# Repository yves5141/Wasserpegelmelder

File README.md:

# Wasserpegelmelder

## Übersicht

Der **Wasserpegelmelder** ist ein eigenständiges Überwachungssystem zur Frühwarnung vor Hochwasser. Das Gerät kann an Brücken montiert werden und misst kontinuierlich den Wasserstand des Flusses. Bei Überschreiten kritischer Schwellwerte wird automatisch eine Warnung versendet.

## Funktionsweise

Der Ultraschallsensor JSN-SR04 misst den Abstand vom Sensor zur Wasseroberfläche. Auf Basis dieses Abstands und der Neigung wird der aktuelle Wasserstand berechnet. Das System überwacht dabei:

- **Wasserstand**: kritisch falls >=95 cm (Hälfte der Flussbett-Tiefe von 190 cm)
- **Anstieg**: kritisch falls >=95 cm/h

Bei Erreichen/Überschreiten dieser Werte wird eine Warnmeldung per Telegram versendet.

## Hardware

Das System basiert auf einem **ESP32-WROOM-32U** und verfügt über:

| Komponente | Beschreibung |
|------------|--------------|
| JSN-SR04T | Ultraschallsensor für Wasserstandsmessung |
| LoRa Ra-02 | Funkmodul für zusätzliche Langstreckenkommunikation |
| CN3791 MPPT | Solarladeregler für 9V Solarzelle (1,17W) |
| TPS63901 | Buck-Boost Regler für 3,3V |
| TPS63802 | Buck-Boost Regler für 5V |
| 18650 | Akkuhalterungen für Akkubetrieb |

### JSN-SR04T

## Betriebsmodi

### Modus 1 - Messung
Das Gerät führt alle 20 Sekunden Messungen durch und geht zwischen den Messungen in den Deep-Sleep Modus, um Strom zu sparen. Keine WLAN-Verbindung wird hergestellt.

### Modus 2 - Fernsteuerung
Alle 5 Minuten wird eine WLAN-Verbindung hergestellt, um auf eingehende Telegram-Befehle zu prüfen und ggf. zu antworten. Anschließend geht das Gerät wieder in den Deep-Sleep Modus.

## Telegram-Befehle

Das Gerät verfügt über einen integrierten Telegram-Bot mit folgenden Befehlen:

| Befehl | Parameter | Ausgabe |
|--------|-----------|---------|
| `/meldung` | - | Statusbericht mit aktuellem Wasserstand und Anstiegsgeschwindigkeit |
| `/update` | angehangene FW-Datei | Firmware-Update |

Nur Nachrichten von autorisierten User-IDs werden entgegengenommen und beantwortet.

## Energieeffizienz

Durch Deep-Sleep-Modi und das Abschalten von nicht benötigten Spannungsreglern wird der Stromverbrauch minimiert. Das System ist so ausgelegt, dass es durch die Solarzelle und die 18650 Akkus langfristig eigenständig betrieben werden kann.

## Anwendungsbereich

Das System ist für den Einsatz an einer Brücke gedacht:
- Vorwarnung bei steigendem Wasserstand
- Beobachtung von Anstiegsgeschwindigkeiten
- Langzeitüberwachung des Wasserpegels

Die Installation erfolgt einfach am Geländer mit einer Neigung von ca. 45° zum Lot. Dieser Winkel ergibt sich aus dem Streuwinkel des Sensors zzgl. Toleranz.

## Status und Ausblick

Die Hardwaretests sind abgeschlossen.
Die Softwareimplementierung befindet sich noch in Arbeit.

## Technische Hintergründe

Das Projekt basiert auf einem ESP32-WROOM-32U Modul. Als primäre Kommunikationsschnittstelle dient das integrierte WLAN des ESP32.
Falls lokal kein Hotspot verfügbar ist, kann alternativ auch ein LoRa Funkmodul genutzt werden.
Im Ordner "Hardware" findet sich das KiCAD Projekt für die Hardware.

## 3D Render eines vollbestückten Melders

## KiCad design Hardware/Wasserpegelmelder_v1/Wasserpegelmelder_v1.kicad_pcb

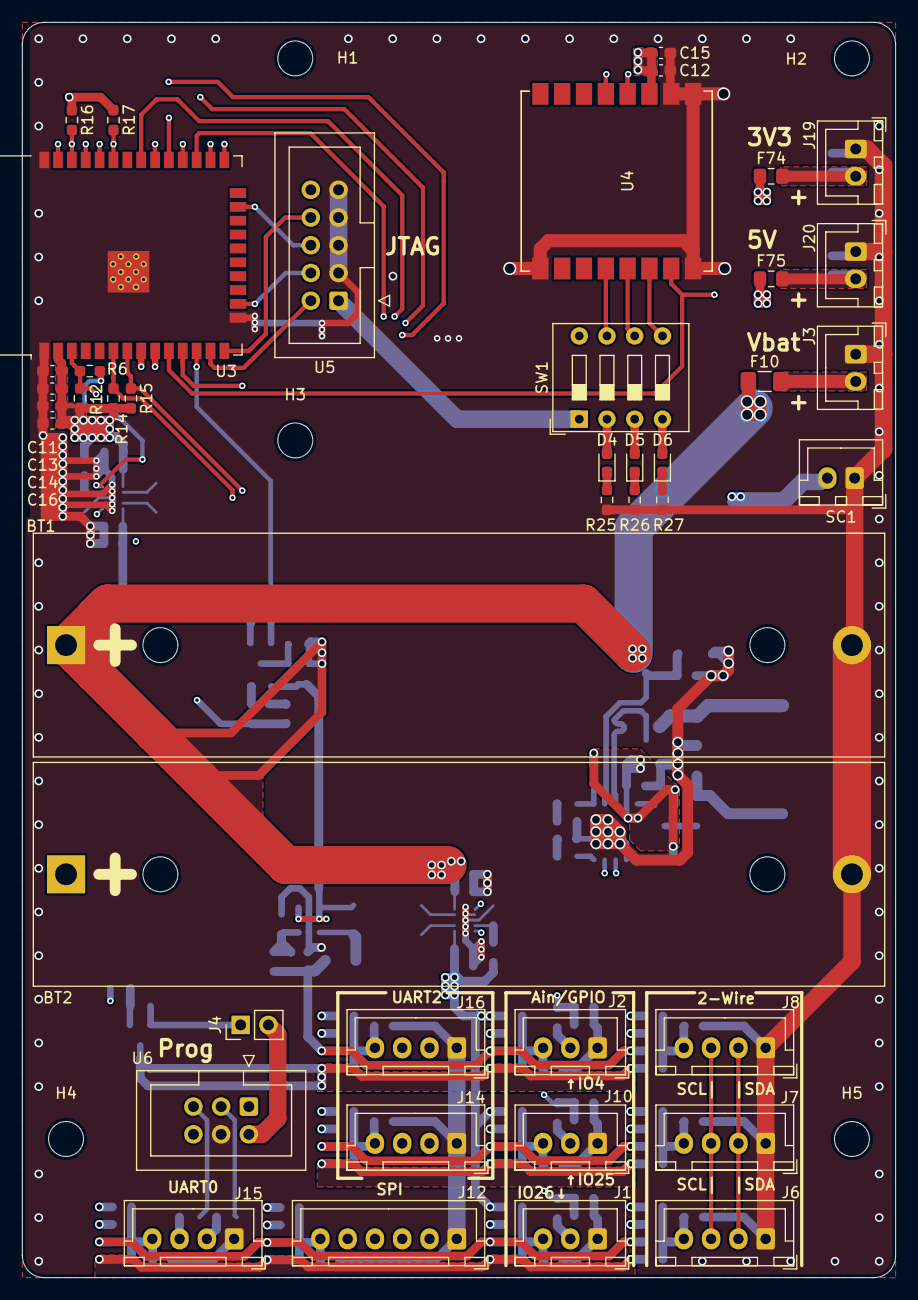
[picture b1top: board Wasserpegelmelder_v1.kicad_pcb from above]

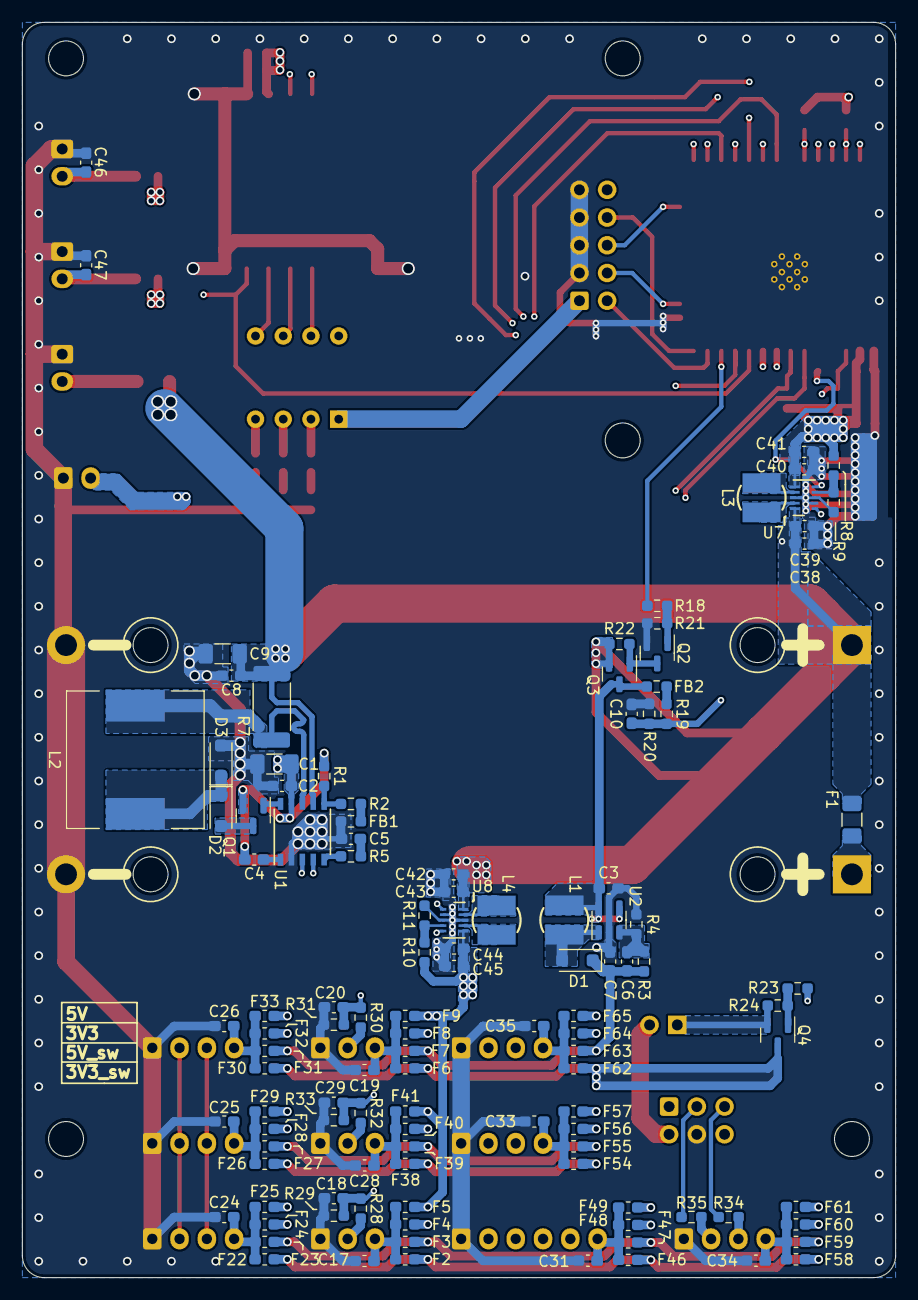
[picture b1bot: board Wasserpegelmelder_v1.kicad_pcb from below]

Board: 4 copper layers, 80.0 x 115.0 mm, 164 parts (116 on the bottom side), 81 nets.

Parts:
BT1, BT2: Battery_Cell; BatteryHolder_1x_18650
C1, C9: 100µF; C_1206_3216Metric_Pad1.33x1.80mm_HandSolder
C2, C4, C8, C11, C12, C39, C40, C43, C44: 100nF; C_0603_1608Metric_Pad1.08x0.95mm_HandSolder
C3: 10µF; C_0603_1608Metric_Pad1.08x0.95mm_HandSolder
C5: 220nF; C_0603_1608Metric_Pad1.08x0.95mm_HandSolder
C6: 71nF; C_0603_1608Metric_Pad1.08x0.95mm_HandSolder
C7, C13: 1µF; C_0603_1608Metric_Pad1.08x0.95mm_HandSolder
C10, C18, C20, C29: 10nF; C_0603_1608Metric_Pad1.08x0.95mm_HandSolder
C14, C15, C16, C17, C19, C24, C25, C26, C28, C31, C33, C34, C35, C38, C41, C42, C45, C46, C47: 47µF; C_0603_1608Metric_Pad1.08x0.95mm_HandSolder
D1, D2, D3: D_Schottky; D_SOD-123F
D4, D5, D6: LED; LED_0603_1608Metric_Pad1.05x0.95mm_HandSolder
F1: 2A; Fuse_1206_3216Metric_Pad1.42x1.75mm_HandSolder
F2, F3, F4, F5, F6, F7, F8, F9, F22, F23, F24, F25, F26, F27, F28, F29, F30, F31, F32, F33, F38, F39, F40, F41, F46, F47, F48, F49, F54, F55, F56, F57, F58, F59, F60, F61, F62, F63, F64, F65: 100mA; Fuse_0603_1608Metric_Pad1.05x0.95mm_HandSolder
F10: 3A; Fuse_1206_3216Metric_Pad1.42x1.75mm_HandSolder
F74, F75: 100mA; Fuse_0805_2012Metric_Pad1.15x1.40mm_HandSolder
FB1, FB2: FerriteBead; R_0603_1608Metric_Pad0.98x0.95mm_HandSolder
H1, H2, H3, H4, H5: MountingHole; MountingHole_3.2mm_M3
J1, J2, J10: IO_ADC; JST_XH_B3B-XH-A_1x03_P2.50mm_Vertical
J3: BatterySupply; JST_XH_B2B-XH-A_1x02_P2.50mm_Vertical
J4: Prog_Jumper; PinHeader_1x02_P2.54mm_Vertical
J6, J7, J8: IO19_IO23; JST_XH_B4B-XH-A_1x04_P2.50mm_Vertical
J12: SPI_Connector; JST_XH_B6B-XH-A_1x06_P2.50mm_Vertical
J14, J16: UART2; JST_XH_B4B-XH-A_1x04_P2.50mm_Vertical
J15: UART0; JST_XH_B4B-XH-A_1x04_P2.50mm_Vertical
J19, J20: nonSwitchedVoltage; JST_XH_B2B-XH-A_1x02_P2.50mm_Vertical
L1: 10µH; CD32_Inductor
L2: 47µH; L_12x12mm_H8mm
L3, L4: 2.2µH; CD32_Inductor
Q1, Q3, Q4: AO3401A; SOT-23
Q2: AO3400A; SOT-23
R1, R2, R3, R4, R8, R9, R10, R11, R19, R20, R25, R26, R27, R28, R29, R30, R31, R32, R33: R; R_0603_1608Metric_Pad0.98x0.95mm_HandSolder
R5: 120R; R_0603_1608Metric_Pad0.98x0.95mm_HandSolder
R6: 0R; R_0603_1608Metric_Pad0.98x0.95mm_HandSolder
R7: R060; R_2512_6332Metric_Pad1.40x3.35mm_HandSolder
R12: 100k; R_0603_1608Metric_Pad0.98x0.95mm_HandSolder
R14, R15: 1M; R_0603_1608Metric_Pad0.98x0.95mm_HandSolder
R16, R17, R34, R35: 1k; R_0603_1608Metric_Pad0.98x0.95mm_HandSolder
R18, R23: 150R; R_0603_1608Metric_Pad0.98x0.95mm_HandSolder
R21, R22, R24: 10k; R_0603_1608Metric_Pad0.98x0.95mm_HandSolder
SC1: 9V_Solar_Cell; JST_XH_B2B-XH-A_1x02_P2.50mm_Vertical
SW1: SW_DIP_x04; SW_DIP_SPSTx04_Slide_9.78x12.34mm_W7.62mm_P2.54mm
U1: SSOP-10_3.9x4.9mm_P1.00mm
U2: TPS61041DBV; SOT-23-5
U3: ESP32-WROOM-32D
U4: Ai-Thinker-Ra-02; Ai-Thinker-Ra-02-LoRa
U5: IDC-Header_2x05_P2.54mm_Vertical
U6: ESP32_Debugger_Prog_IDC-Header_2x03_P2.54mm_Vertical
U7, U8: TPS63802_DFN-10-1EP_2x3mm_P0.5mm_EP0.64x2.4mm

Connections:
3V3_switch: R23.1, U3.8 (IO32)
3V3_switched: F2.1, F6.1, F22.1, F26.1, F30.1, F38.1, F46.1, F54.1, F58.1, F62.1, Q4.3 (D)
5V_switched: C6.1, C7.1, D1.1 (K), F3.1, F7.1, F23.1, F27.1, F31.1, F39.1, F47.1, F55.1, F59.1, F63.1, R3.1
+3V3: C11.1, C12.1, C13.1, C14.1, C15.1, C16.1, C40.1, C41.1, F4.1, F8.1, F24.1, F28.1, F32.1, F40.1, F48.1, F56.1, F60.1, F64.1, F74.1, J4.1, Q4.2 (S), R8.1, R12.2, R14.2, R15.2, R16.1, R17.1, R24.2, SW1.8, U3.2 (VDD), U4.3 (VDD), U7.6 (Vout)
+5V: C44.1, C45.1, F5.1, F9.1, F25.1, F29.1, F33.1, F41.1, F49.1, F57.1, F61.1, F65.1, F75.1, R10.1, U8.6 (Vout)
+BATT: BT1.1 (+), C8.1, C9.1, C38.1, C39.1, C42.1, C43.1, F1.1, F10.1, Q3.2 (S), R7.2, R22.1, U1.7 (BAT), U7.1 (En), U7.10 (Vin), U8.1 (En), U8.10 (Vin)
/Sense_P: L2.2, R7.1, U1.8 (CSP)
/TPS63802_voltage_regulator1/FB: R10.2, R11.1, U8.4 (FB)
/TPS63802_voltage_regulator/FB: R8.2, R9.1, U7.4 (FB)
/TPS63802_voltage_regulator/PG: R6.2, U7.5 (PG)
Ain_Vbat: C10.1, R19.2, R20.1, U3.9 (IO33)
EN: R6.1, R12.1, U3.3 (EN), U6.1 (EN)
GND: BT1.2 (-), BT2.2 (-), C1.2, C2.2, C3.2, C5.2, C7.2, C8.2, C9.2, C10.2, C11.2, C12.2, C13.2, C14.2, C15.2, C16.2, C17.2, C18.2, C19.2, C20.2, C24.2, C25.2, C26.2, C28.2, C29.2, C31.2, C33.2, C34.2, C35.2, C38.2, C39.2, C40.2, C41.2, C42.2, C43.2, C44.2, C45.2, C46.2, C47.2, D3.2 (A), FB1.2, J1.1, J2.1, J3.1, J6.1, J7.1, J8.1, J10.1, J12.1, J14.1, J15.1, J16.1, J19.1, J20.1, Q2.2 (S), R4.2, R9.2, R11.2, R20.2, R21.2, R25.2, R26.2, R27.2, R29.1, R31.1, R33.1, SC1.1 (+), U1.2 (GND), U2.2 (GND), U3.1 (GND), U3.15 (GND), U3.38 (GND), U3.39 (GND), U4.1 (GND), U4.2 (GND), U4.9 (GND), U4.16 (GND), U5.3 (GND), U5.5 (GND), U5.7 (GND), U5.9 (GND), U6.4 (GND), U7.2 (Mode), U7.3 (AGND), U7.8 (GND), U8.2 (Mode), U8.3 (AGND), U8.8 (GND)
IO0: U3.25 (IO0), U6.6 (IO0)
IO4: C20.1, R30.1, R31.2, U3.26 (IO4), U4.5 (DIO0)
IO5: J12.5, U3.29 (IO5)
IO25: C29.1, R32.1, R33.2, U3.10 (IO25), U4.15 (~NSS)
IO26: C18.1, R28.1, R29.2, U3.11 (IO26), U4.4 (~RESET)
MISO: J12.3, SW1.6, U3.31 (IO19), U4.13 (MISO)
MOSI: J12.4, SW1.5, U3.37 (IO23), U4.14 (MOSI)
unnamed: BT2.1 (+), F1.2
unnamed: C5.1, R5.2
unnamed: D1.2 (A), L1.2, U2.1 (SW)
unnamed: D2.2 (A), Q1.3 (D)
unnamed: D2.1 (K), D3.1 (K), L2.1
unnamed: D4.2 (A), SW1.2
unnamed: D4.1 (K), R25.1
unnamed: D5.2 (A), SW1.3
unnamed: D5.1 (K), R26.1
unnamed: D6.2 (A), SW1.4
unnamed: D6.1 (K), R27.1
unnamed: FB1.1, R2.2
unnamed: FB2.1, R19.1
unnamed: J1.2, R28.2
unnamed: C17.1, F2.2, F3.2, F4.2, F5.2, J1.3
unnamed: J2.2, R30.2
unnamed: C19.1, F6.2, F7.2, F8.2, F9.2, J2.3
unnamed: F10.2, J3.2
unnamed: J4.2, U6.2 (Vcc)
unnamed: C24.1, F22.2, F23.2, F24.2, F25.2, J6.4
unnamed: C25.1, F26.2, F27.2, F28.2, F29.2, J7.4
unnamed: C26.1, F30.2, F31.2, F32.2, F33.2, J8.4
unnamed: J10.2, R32.2
unnamed: C28.1, F38.2, F39.2, F40.2, F41.2, J10.3
unnamed: C31.1, F46.2, F47.2, F48.2, F49.2, J12.6
unnamed: C33.1, F54.2, F55.2, F56.2, F57.2, J14.4
unnamed: J15.2, R35.2
unnamed: J15.3, R34.2
unnamed: C34.1, F58.2, F59.2, F60.2, F61.2, J15.4
unnamed: C35.1, F62.2, F63.2, F64.2, F65.2, J16.4
unnamed: C46.1, F74.2, J19.2
unnamed: C47.1, F75.2, J20.2
unnamed: Q1.1 (G), U1.10 (DRV)
unnamed: C1.1, C2.1, C4.1, Q1.2 (S), R1.1, SC1.2 (-), U1.9 (Vcc)
unnamed: Q2.3 (D), Q3.1 (G), R22.2
unnamed: Q2.1 (G), R18.1, R21.1
unnamed: Q4.1 (G), R23.2, R24.1
unnamed: R5.1, U1.5 (COM)
unnamed: R1.2, R2.1, U1.6 (MPPT)
unnamed: C4.2, U1.1 (VG)
unnamed: C6.2, R3.2, R4.1, U2.3 (FB)
unnamed: SW1.1, U5.1 (VJTAG)
unnamed: L3.1, U7.9 (L1)
unnamed: L3.2, U7.7 (L2)
unnamed: L4.1, U8.9 (L1)
unnamed: L4.2, U8.7 (L2)
Rx0: R34.1, U3.34 (RXD0/IO3), U6.5 (Rx)
Rx2: J14.3, J16.3, U3.27 (IO16)
SCK: J12.2, SW1.7, U3.30 (IO18), U4.12 (SCK)
SCL: J6.3, J7.3, J8.3, R16.2, U3.36 (IO22)
SDA: J6.2, J7.2, J8.2, R17.2, U3.33 (IO21)
TCK: U3.16 (IO13), U5.4 (TCK)
TDI: U3.14 (IO12), U5.8 (TDI)
TDO: U3.23 (IO15), U5.6 (TDO)
TMS: U3.13 (IO14), U5.2 (TMS)
Tx0: R35.1, U3.35 (TXD0/IO1), U6.3 (Tx)
Tx2: J14.2, J16.2, U3.28 (IO17)
Vbat_switch: R18.2, U3.12 (IO27)
Vbat_switched: C3.1, FB2.2, L1.1, Q3.3 (D), U2.4 (EN), U2.5 (VIN)
_CHRG: R15.1, U1.3 (_CHRG), U3.7 (IO35)
_DONE: R14.1, U1.4 (_DONE), U3.6 (IO34)

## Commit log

2026-03-04 initial commit, v0.3
